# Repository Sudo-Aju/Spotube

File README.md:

<div align="center">

# 

a physical spotify controller

### *a dedicated physical interface for controlling spotify.*

</div>

---

# Overview

**spotube** is a compact physical spotify controller built around an **esp32-s3**, 1.5" lcd, mechanical switches, and a rotary encoder.

it provides physical controls for spotify playback while displaying the current track.

---

# Gallery

<div align="center">

</div>

---

# Features

* spotify integration
* esp32-s3
* 1.5" ips display
* cherry mx switches
* ec11 rotary encoder
* wi-fi
* custom pcb
* custom enclosure
* physical playback controls

---

# Hardware stack

| component    | description             |
| ------------ | ----------------------- |
| mcu          | waveshare esp32-s3 mini |
| display      | waveshare 1.5" ips lcd  |
| switches     | cherry mx               |
| encoder      | ec11                    |
| connectivity | wi-fi                   |
| pcb          | custom kiCad design     |
| case         | custom 3d printed       |

---

# Assembly

## 1. order the pcb

generate gerbers from:

```bash
PCB/Spotube.kicad_pcb
```

and send them to your preferred manufacturer.

## 2. order components

all components are listed in:

```bash
BOM.csv
```

## 3. assemble

* solder the switches
* solder the ec11 encoder
* install the esp32-s3
* connect the display
* assemble the enclosure
* install the keycaps

---

# firmware

firmware is located in:

```bash
spotube.ino
```

the firmware handles:

* wi-fi
* spotify api
* display
* buttons
* rotary encoder

## setup

configure your:

```cpp
wifi ssid
wifi password
spotify client id
spotify client secret
```

then upload the firmware to the esp32-s3.

---

# PCB

designed in **KiCad**.

```bash
PCB/
├── Spotube.kicad_pcb
├── Spotube.kicad_sch
├── Spotube.kicad_pro
└── Spotube.kicad_prl
```

<div align="center">

</div>

---

# Enclosure

the complete assembly is available as:

```bash
Assembly.step
```

and the stl files for enclosures is available as:

```bash
Bottom.stl
Upper.stl
Rod.stl
```

designed around the custom pcb and components.

---

# BOM

|Name                                                                                   |Purpose        |Cost Per Item (USD)|Quantity|Total (USD)|Link                                                                                                                                                                                                                                                                                                                                                                                                                                                                                                                                                                          |Distributor|
|---------------------------------------------------------------------------------------|---------------|-------------------|--------|-----------|------------------------------------------------------------------------------------------------------------------------------------------------------------------------------------------------------------------------------------------------------------------------------------------------------------------------------------------------------------------------------------------------------------------------------------------------------------------------------------------------------------------------------------------------------------------------------|-----------|
|3D print model                                                                         |Shell          |5.0                |1       |5.0        |https://github.com/hackclub/print-legion                                                                                                                                                                                                                                                                                                                                                                                                                                                                                                                                      |Hack Club  |
|Cherry MX Keycaps                                                                      |Keycaps        |6.0                |1       |6.0        |https://www.amazon.in/STYLEHEAVEN-Transparent-Keycaps-Cherry-Switches/dp/B0GFP1XJ9Z/ref=sr_1_3?crid=DYB9DOR1TQBR&dib=eyJ2IjoiMSJ9.kKc3HdH17AhE-nTQrQ1SxfVaJhYmeFbPm0835eVz_-jbeImT-htLy8qY5z9y7LFMVcU5GMdK1seMkgmHiR4wWpi1BgtYqCacbU8EvAMouMm7CIndQuxGhQM03HZ5q1YC1rxEzez9aDCuzcTNcX6JDWGt8_kTfs1JOH-BJ0gKga4v_X3wMwq5lh2IEx95DAljB56USbKK-cMQQL0NlOBpbdPy96U8AAuc-0rmg1aAkgo.8iI3E4B-61cjV9iN_8wTP24XBDafzPccAuC3eiihFm8&dib_tag=se&keywords=cherry+mx+keycaps&nsdOptOutParam=true&qid=1773942374&sprefix=cherry+mx+keyca%2Caps%2C375&sr=8-3                                 |Amazon     |
|Cherry MX Switches                                                                     |Switches       |4.0                |1       |4.0        |https://neomacro.in/products/cherry-mx-switches?srsltid=AfmBOopQB-NQ1BO0dVkkvkxVeaQVPTGoN2zvkJHoIvh3QNb6hdRFlXtS                                                                                                                                                                                                                                                                                                                                                                                                                                                              |Neo Macro  |
|M3X4 mm Brass Heat Set Threaded Round Insert Nut - Pack of 6                           |Heatset Inserts|1.0                |1       |1.0        |https://www.amazon.in/M3X4-Brass-Threaded-Round-Insert/dp/B0B9NL8F74/ref=sr_1_6?crid=4XHSG7DE82FX&dib=eyJ2IjoiMSJ9.jSf9pEXSTtLSBrCZPvV8rjy5sJiwLvEN3PXR5QozJPsAiY0a3zu6d2eMFlCtvwc3lazSN3qwL78W-59c-F2lxC8eSm_g7yI2pQcVhqhLF0ZTlcaxr_mBZh80dUTecpa2n2oi8dVloWKQzb8cnK1K6XzuL9LXztnVKEaTjiPcTQCJJVEKcjAfRsyneHSKDAbe3HTdYqj45szwxJxZ59RBY0f4fnIMMKMSxA-nZUmDnciH63nYQ_eTNyiBXuaOVkBy9CxHedxJKnfBrpx4WTrILm3y449EAYZIIWevf4pucFc.ck8xHBHMe4U-TGfCyeApORo9GM7ryFF2eu3gQ-_vovg&dib_tag=se&keywords=M3+Heatset+inserts&qid=1773942041&sprefix=m3+heatset+inserts%2Caps%2C364&sr=8-6|Amazon     |
|Waveshare 1.5inch LCD Module (240×280 IPS)                                             |Screen         |9.49               |1       |9.49       |https://www.waveshare.com/1.5inch-lcd-module.htm                                                                                                                                                                                                                                                                                                                                                                                                                                                                                                                              |Waveshare  |
|Waveshare ESP32-S3 Mini Development Board based on ESP32-S3FH4R2 4MB Flash & 2MB PS RAM|Dev Board      |6.82               |1       |6.82       |https://robu.in/product/waveshare-esp32-s3-mini-development-board-based-on-esp32-s3fh4r2-4mb-flash-and-2mb-ps-ram-without-headers-and-adapter-board-fpc-cable/                                                                                                                                                                                                                                                                                                                                                                                                                |Robu.in    |
|EC11 Rotary Encoder Module with Knob Cap                                               |Rotary Input   |0.98               |1       |0.98       |https://robu.in/product/EC11%20Rotary%20Encoder%20Module%20with%20Knob%20Cap%20for%20Development%20Boards/                                                                                                                                                                                                                                                                                                                                                                                                                                                                    |Robu.in    |

---

# Repository

```text
Spotube/
├── PCB/
├── CAD/
├── Media/
├── Firmware/spotube.ino
├── BOM.csv
└── README.md
```

---

# Current status

* [x] concept
* [x] pcb
* [x] schematic
* [x] enclosure
* [x] firmware
* [ ] final build
* [ ] complete spotify controls

---

# Contributing

contributions and suggestions are welcome.

```bash
git clone https://github.com/Sudo-Aju/Spotube.git
cd Spotube
```

fork → modify → commit → pull request

---

# Creator

### Azmeer Pirani

17 • India • @macondo

built with a love for:

* hardware
* pcb design
* music
* embedded systems
* experimental products

---

# License

This project is licensed under the **MIT license**.

---

<div align="center">

# Spotube

### *your music. your controls.*

</div>

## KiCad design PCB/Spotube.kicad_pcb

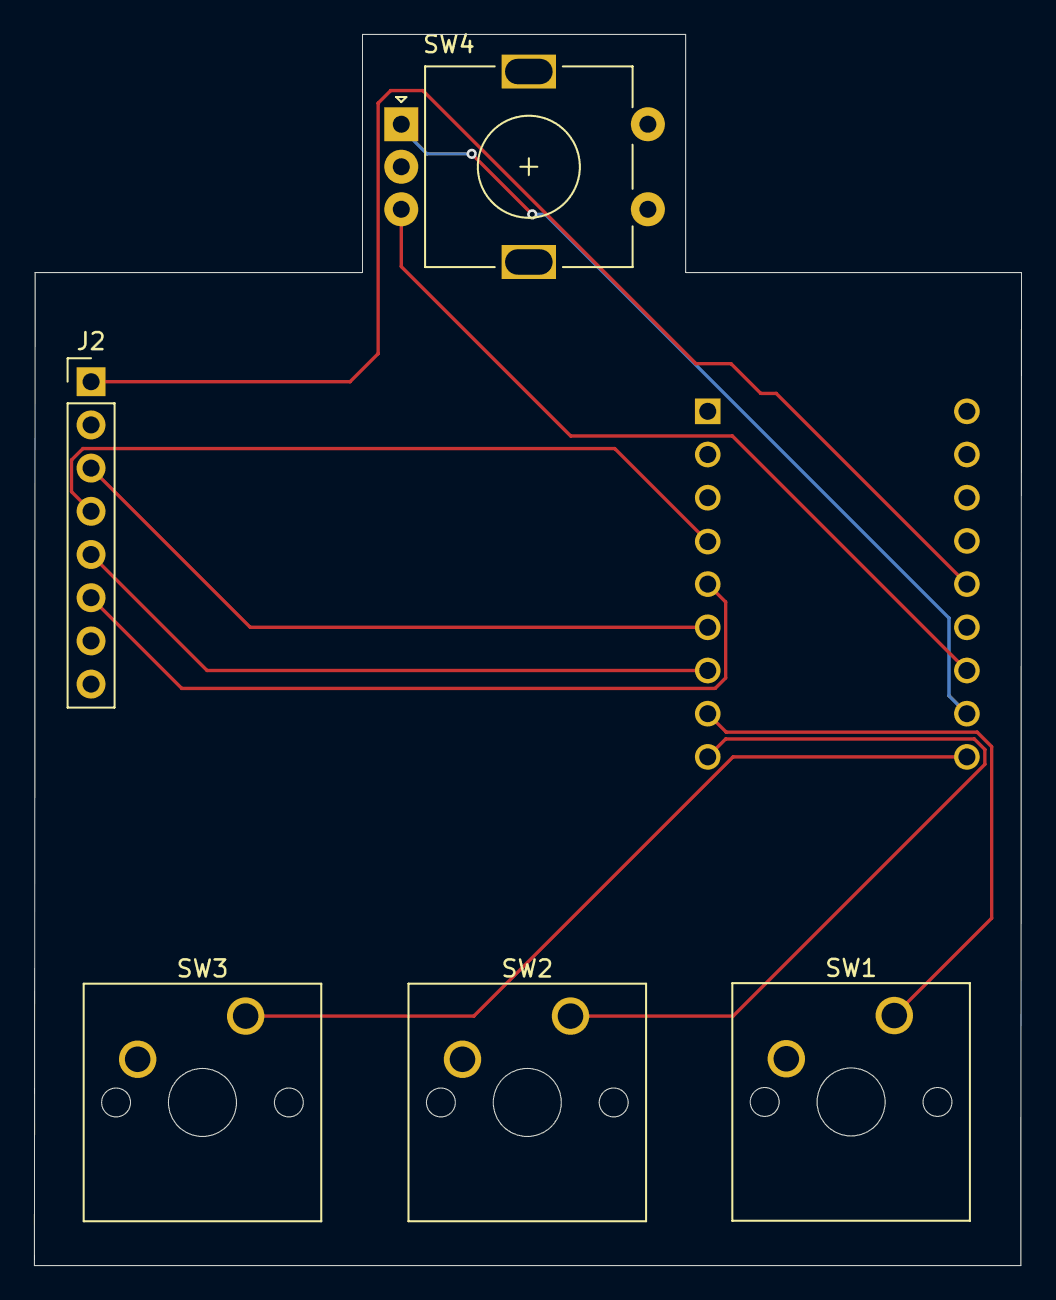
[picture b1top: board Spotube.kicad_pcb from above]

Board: 2 copper layers, 58.0 x 72.4 mm, 6 parts (1 on the bottom side), 11 nets.

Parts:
J2: Conn_01x08_Socket; PinHeader_1x08_P2.54mm_Vertical
SW1, SW2, SW3: SW_Push; SW_Cherry_MX_1.00u_PCB
SW4: RotaryEncoder; RotaryEncoder_Alps_EC11E-Switch_Vertical_H20mm
U1: ESP32-S3-SuperMini

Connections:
+3V3: J2.1, U1.3 (3V3)
/CLK: J2.4, U1.13 (GPIO_4)
/CS: J2.5, U1.10 (GPIO_7)
/DC: J2.6, U1.12 (GPIO_5)
/DIN: J2.3, U1.11 (GPIO_6)
/GPIO_8: SW1.1, U1.9 (GPIO_8)
/GPIO_9: SW2.1, U1.8 (GPIO_9)
/GPIO_10: SW3.1, U1.7 (GPIO_10)
/GPIO_11: SW4.A, U1.6 (GPIO_11)
/GPIO_12: SW4.B, U1.5 (GPIO_12)
GND: J2.2, SW1.2, SW2.2, SW3.2, SW4.C, U1.2 (GND)

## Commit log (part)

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2026-03-19 Rename Model.stl to CAD/Print.stl
2026-03-19 Rename ModelStep.step to CAD/Print.step
2026-03-19 Rename Spotube.step.zip to CAD/FullAssembly.zip
